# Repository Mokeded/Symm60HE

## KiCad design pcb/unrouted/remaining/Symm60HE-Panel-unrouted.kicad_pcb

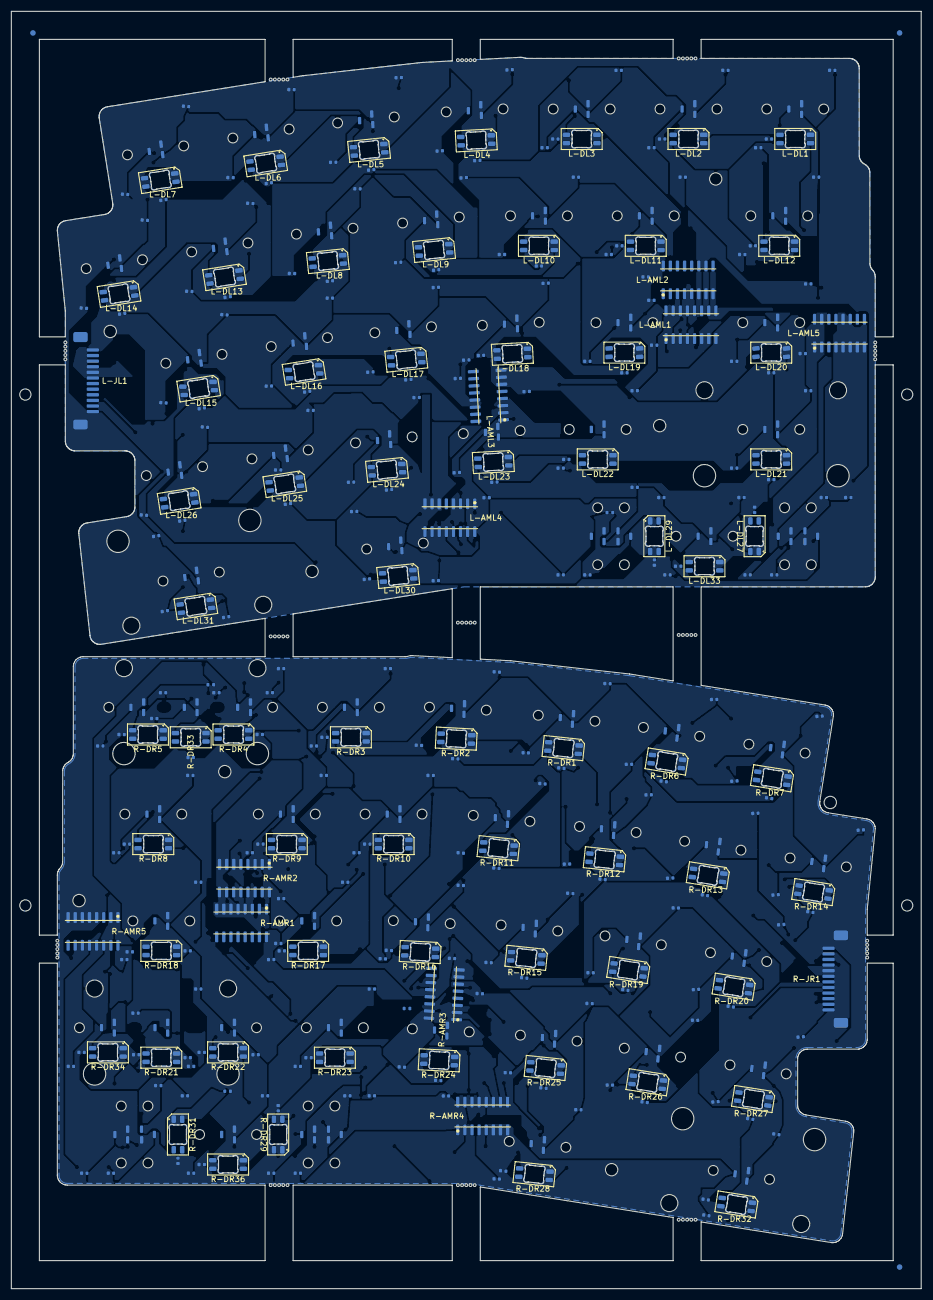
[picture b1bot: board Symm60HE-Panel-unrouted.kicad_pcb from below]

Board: 2 copper layers, 162.3 x 227.8 mm, 448 parts (366 on the bottom side), 154 nets, no tracks yet.

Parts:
FID1, FID2, FID3: FIDUCIAL_1MM_BCU; Fiducial_1mm_BCu
L-AML1, L-AML2, L-AML3, L-AML4, L-AML5: SN74LV4051A; AM1_SOIC-16_3.9x9.9mm_P1.27mm
L-CL1A, L-CL2A, L-CL3A, L-CL4A, L-CL5A, L-CL6A, L-CL7A, L-CL8A, L-CL9A, L-CL10A, L-CL11A, L-CL12A, L-CL13A, L-CL14A, L-CL15A, L-CL16A, L-CL17A, L-CL18A, L-CL19A, L-CL20A, L-CL21A, L-CL22A, L-CL23A, L-CL24A, L-CL25A, L-CL26A, L-CL27A, L-CL28A, L-CL29A, L-CL30A, L-CL31A, L-CL32A, L-CL33A: 100n; C1_C_0402_1005Metric
L-CL1B, L-CL2B, L-CL3B, L-CL4B, L-CL5B, L-CL6B, L-CL7B, L-CL8B, L-CL9B, L-CL10B, L-CL11B, L-CL12B, L-CL13B, L-CL14B, L-CL15B, L-CL16B, L-CL17B, L-CL18B, L-CL19B, L-CL20B, L-CL21B, L-CL22B, L-CL23B, L-CL24B, L-CL25B, L-CL26B, L-CL27B, L-CL28B, L-CL29B, L-CL30B, L-CL31B, L-CL32B, L-CL33B: 4.7n; C1_C_0402_1005Metric
L-CML1, L-CML2, L-CML3, L-CML4, L-CML5: 100n; C1_C_0402_1005Metric
L-CRGBL1, L-CRGBL2, L-CRGBL3, L-CRGBL4, L-CRGBL5, L-CRGBL6, L-CRGBL7, L-CRGBL8, L-CRGBL9, L-CRGBL10, L-CRGBL11, L-CRGBL12, L-CRGBL13, L-CRGBL14, L-CRGBL15, L-CRGBL16, L-CRGBL17, L-CRGBL18, L-CRGBL19, L-CRGBL20, L-CRGBL21, L-CRGBL22, L-CRGBL23, L-CRGBL24, L-CRGBL25, L-CRGBL26, L-CRGBL27, L-CRGBL29, L-CRGBL30, L-CRGBL31, L-CRGBL33: 100n; C1_C_0402_1005Metric
L-DL1, L-DL2, L-DL3, L-DL4, L-DL5, L-DL6, L-DL7, L-DL8, L-DL9, L-DL10, L-DL11, L-DL12, L-DL13, L-DL14, L-DL15, L-DL16, L-DL17, L-DL18, L-DL19, L-DL20, L-DL21, L-DL22, L-DL23, L-DL24, L-DL25, L-DL26, L-DL27, L-DL29, L-DL30, L-DL31, L-DL33: SK6812MINI-E; SK6812MINI-E_ReverseMount
L-HEL1, L-HEL2, L-HEL3, L-HEL4, L-HEL5, L-HEL6, L-HEL7, L-HEL9, L-HEL10, L-HEL11, L-HEL12, L-HEL13, L-HEL14, L-HEL16, L-HEL17, L-HEL18, L-HEL19, L-HEL20, L-HEL22, L-HEL23, L-HEL24, L-HEL25, L-HEL26, L-HEL27, L-HEL29, L-HEL31: MT9102ET; HE_KEY_1.00u
L-HEL8, L-HEL28, L-HEL30, L-HEL32: MT9102ET; HE_KEY_1.50u
L-HEL15: MT9102ET; HE_KEY_1.75u
L-HEL21, L-HEL33: MT9102ET; HE_KEY_2.25u
L-JL1: FFC_12P; FFC_12P_1.00mm_TopContact
L-MHL1, L-MHL2, L-MHL3, L-MHL4: M2_NPTH; MountingHole_2.2mm_M2_NPTH
L-RBPL29: 0R_DNP; R3_R_0402_1005Metric
L-SL1, L-SL2: STAB_MX; STABILIZER_MX_2U
MB1, MB2, MB3, MB4, MB5, MB6, MB7, MB8, MB9, MB10, MB11, MB12, MB13, MB14, MB15, MB16, MB17, MB18, MB19, MB20, MB21, MB22, MB23, MB24, MB25, MB26, MB27, MB28, MB29, MB30, MB31, MB32, MB33, MB34, MB35, MB36, MB37, MB38, MB39, MB40, MB41, MB42, MB43, MB44, MB45, MB46, MB47, MB48, MB49, MB50, MB51, MB52, MB53, MB54, MB55, MB56, MB57, MB58, MB59, MB60, MB61, MB62, MB63, MB64, MB65: MOUSE_BITE_0.5MM; MouseBite_0.5mm
R-AMR1, R-AMR2, R-AMR3, R-AMR4, R-AMR5: SN74LV4051A; AM1_SOIC-16_3.9x9.9mm_P1.27mm
R-CMR1, R-CMR2, R-CMR3, R-CMR4, R-CMR5: 100n; C1_C_0402_1005Metric
R-CR1A, R-CR2A, R-CR3A, R-CR4A, R-CR5A, R-CR6A, R-CR7A, R-CR8A, R-CR9A, R-CR10A, R-CR11A, R-CR12A, R-CR13A, R-CR14A, R-CR15A, R-CR16A, R-CR17A, R-CR18A, R-CR19A, R-CR20A, R-CR21A, R-CR22A, R-CR23A, R-CR24A, R-CR25A, R-CR26A, R-CR27A, R-CR28A, R-CR29A, R-CR30A, R-CR31A, R-CR32A, R-CR33A, R-CR34A, R-CR35A, R-CR36A: 100n; C1_C_0402_1005Metric
R-CR1B, R-CR2B, R-CR3B, R-CR4B, R-CR5B, R-CR6B, R-CR7B, R-CR8B, R-CR9B, R-CR10B, R-CR11B, R-CR12B, R-CR13B, R-CR14B, R-CR15B, R-CR16B, R-CR17B, R-CR18B, R-CR19B, R-CR20B, R-CR21B, R-CR22B, R-CR23B, R-CR24B, R-CR25B, R-CR26B, R-CR27B, R-CR28B, R-CR29B, R-CR30B, R-CR31B, R-CR32B, R-CR33B, R-CR34B, R-CR35B, R-CR36B: 4.7n; C1_C_0402_1005Metric
R-CRGBR1, R-CRGBR2, R-CRGBR3, R-CRGBR4, R-CRGBR5, R-CRGBR6, R-CRGBR7, R-CRGBR8, R-CRGBR9, R-CRGBR10, R-CRGBR11, R-CRGBR12, R-CRGBR13, R-CRGBR14, R-CRGBR15, R-CRGBR16, R-CRGBR17, R-CRGBR18, R-CRGBR19, R-CRGBR20, R-CRGBR21, R-CRGBR22, R-CRGBR23, R-CRGBR24, R-CRGBR25, R-CRGBR26, R-CRGBR27, R-CRGBR28, R-CRGBR29, R-CRGBR31, R-CRGBR32, R-CRGBR33, R-CRGBR34, R-CRGBR36: 100n; C1_C_0402_1005Metric
R-DR1, R-DR2, R-DR3, R-DR4, R-DR5, R-DR6, R-DR7, R-DR8, R-DR9, R-DR10, R-DR11, R-DR12, R-DR13, R-DR14, R-DR15, R-DR16, R-DR17, R-DR18, R-DR19, R-DR20, R-DR21, R-DR22, R-DR23, R-DR24, R-DR25, R-DR26, R-DR27, R-DR28, R-DR29, R-DR31, R-DR32, R-DR33, R-DR34, R-DR36: SK6812MINI-E; SK6812MINI-E_ReverseMount
R-HER1, R-HER2, R-HER3, R-HER5, R-HER6, R-HER7, R-HER8, R-HER9, R-HER10, R-HER12, R-HER13, R-HER14, R-HER15, R-HER16, R-HER17, R-HER19, R-HER20, R-HER21, R-HER22, R-HER23, R-HER24, R-HER27, R-HER28, R-HER29, R-HER30, R-HER32, R-HER34: MT9102ET; HE_KEY_1.00u
R-HER4: MT9102ET; HE_KEY_2.00u
R-HER11, R-HER31, R-HER33, R-HER35: MT9102ET; HE_KEY_1.50u
R-HER18: MT9102ET; HE_KEY_1.75u
R-HER25, R-HER36: MT9102ET; HE_KEY_2.25u
R-HER26: MT9102ET; HE_KEY_1.25u
R-JR1: FFC_12P; FFC_12P_1.00mm_TopContact
R-MHR1, R-MHR2, R-MHR3, R-MHR4: M2_NPTH; MountingHole_2.2mm_M2_NPTH
R-RBPR5, R-RBPR24, R-RBPR31: 0R_DNP; R3_R_0402_1005Metric
R-SR1, R-SR2, R-SR3: STAB_MX; STABILIZER_MX_2U
TH1, TH2, TH3, TH4: TOOLING_HOLE_2MM; ToolingHole_2mm_NPTH

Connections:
/L/+3V3A: L-AML1.16, L-AML2.16, L-AML3.16, L-AML4.16, L-AML5.16, L-CL1A.1, L-CL2A.1, L-CL3A.1, L-CL4A.1, L-CL5A.1, L-CL6A.1, L-CL7A.1, L-CL8A.1, L-CL9A.1, L-CL10A.1, L-CL11A.1, L-CL12A.1, L-CL13A.1, L-CL14A.1, L-CL15A.1, L-CL16A.1, L-CL17A.1, L-CL18A.1, L-CL19A.1, L-CL20A.1, L-CL21A.1, L-CL22A.1, L-CL23A.1, L-CL24A.1, L-CL25A.1, L-CL26A.1, L-CL27A.1, L-CL28A.1, L-CL29A.1, L-CL30A.1, L-CL31A.1, L-CL32A.1, L-CL33A.1, L-CML1.1, L-CML2.1, L-CML3.1, L-CML4.1, L-CML5.1, L-HEL1.1, L-HEL2.1, L-HEL3.1, L-HEL4.1, L-HEL5.1, L-HEL6.1, L-HEL7.1, L-HEL8.1, L-HEL9.1, L-HEL10.1, L-HEL11.1, L-HEL12.1, L-HEL13.1, L-HEL14.1, L-HEL15.1, L-HEL16.1, L-HEL17.1, L-HEL18.1, L-HEL19.1, L-HEL20.1, L-HEL21.1, L-HEL22.1, L-HEL23.1, L-HEL24.1, L-HEL25.1, L-HEL26.1, L-HEL27.1, L-HEL28.1, L-HEL29.1, L-HEL30.1, L-HEL31.1, L-HEL32.1, L-HEL33.1, L-JL1.12
/L/ADC_L1: L-AML1.3, L-JL1.6
/L/ADC_L2: L-AML2.3, L-JL1.4
/L/ADC_L3: L-AML3.3, L-JL1.2
/L/ADC_L4: L-AML4.3, L-JL1.1
/L/ADC_L5: L-AML5.3, L-JL1.11
/L/GND: L-AML1.6, L-AML1.7, L-AML1.8, L-AML2.6, L-AML2.7, L-AML2.8, L-AML3.6, L-AML3.7, L-AML3.8, L-AML4.4, L-AML4.6, L-AML4.7, L-AML4.8, L-AML5.1, L-AML5.2, L-AML5.4, L-AML5.5, L-AML5.6, L-AML5.7, L-AML5.8, L-AML5.12, L-AML5.15, L-CL1A.2, L-CL1B.2, L-CL2A.2, L-CL2B.2, L-CL3A.2, L-CL3B.2, L-CL4A.2, L-CL4B.2, L-CL5A.2, L-CL5B.2, L-CL6A.2, L-CL6B.2, L-CL7A.2, L-CL7B.2, L-CL8A.2, L-CL8B.2, L-CL9A.2, L-CL9B.2, L-CL10A.2, L-CL10B.2, L-CL11A.2, L-CL11B.2, L-CL12A.2, L-CL12B.2, L-CL13A.2, L-CL13B.2, L-CL14A.2, L-CL14B.2, L-CL15A.2, L-CL15B.2, L-CL16A.2, L-CL16B.2, L-CL17A.2, L-CL17B.2, L-CL18A.2, L-CL18B.2, L-CL19A.2, L-CL19B.2, L-CL20A.2, L-CL20B.2, L-CL21A.2, L-CL21B.2, L-CL22A.2, L-CL22B.2, L-CL23A.2, L-CL23B.2, L-CL24A.2, L-CL24B.2, L-CL25A.2, L-CL25B.2, L-CL26A.2, L-CL26B.2, L-CL27A.2, L-CL27B.2, L-CL28A.2, L-CL28B.2, L-CL29A.2, L-CL29B.2, L-CL30A.2, L-CL30B.2, L-CL31A.2, L-CL31B.2, L-CL32A.2, L-CL32B.2, L-CL33A.2, L-CL33B.2, L-CML1.2, L-CML2.2, L-CML3.2, L-CML4.2, L-CML5.2, L-CRGBL1.2, L-CRGBL2.2, L-CRGBL3.2, L-CRGBL4.2, L-CRGBL5.2, L-CRGBL6.2, L-CRGBL7.2, L-CRGBL8.2, L-CRGBL9.2, L-CRGBL10.2, L-CRGBL11.2, L-CRGBL12.2, L-CRGBL13.2, L-CRGBL14.2, L-CRGBL15.2, L-CRGBL16.2, L-CRGBL17.2, L-CRGBL18.2, L-CRGBL19.2, L-CRGBL20.2, L-CRGBL21.2, L-CRGBL22.2, L-CRGBL23.2, L-CRGBL24.2, L-CRGBL25.2, L-CRGBL26.2, L-CRGBL27.2, L-CRGBL29.2, L-CRGBL30.2, L-CRGBL31.2, L-CRGBL33.2, L-DL1.1, L-DL2.1, L-DL3.1, L-DL4.1, L-DL5.1, L-DL6.1, L-DL7.1, L-DL8.1, L-DL9.1, L-DL10.1, L-DL11.1, L-DL12.1, L-DL13.1, L-DL14.1, L-DL15.1, L-DL16.1, L-DL17.1, L-DL18.1, L-DL19.1, L-DL20.1, L-DL21.1, L-DL22.1, L-DL23.1, L-DL24.1, L-DL25.1, L-DL26.1, L-DL27.1, L-DL29.1, L-DL30.1, L-DL31.1, L-DL33.1, L-HEL1.2, L-HEL2.2, L-HEL3.2, L-HEL4.2, L-HEL5.2, L-HEL6.2, L-HEL7.2, L-HEL8.2, L-HEL9.2, L-HEL10.2, L-HEL11.2, L-HEL12.2, L-HEL13.2, L-HEL14.2, L-HEL15.2, L-HEL16.2, L-HEL17.2, L-HEL18.2, L-HEL19.2, L-HEL20.2, L-HEL21.2, L-HEL22.2, L-HEL23.2, L-HEL24.2, L-HEL25.2, L-HEL26.2, L-HEL27.2, L-HEL28.2, L-HEL29.2, L-HEL30.2, L-HEL31.2, L-HEL32.2, L-HEL33.2, L-JL1.5
/L/HE_L01: L-AML1.13, L-CL1B.1, L-HEL1.3
/L/HE_L02: L-AML1.14, L-CL2B.1, L-HEL2.3
/L/HE_L03: L-AML1.15, L-CL3B.1, L-HEL3.3
/L/HE_L04: L-AML1.12, L-CL4B.1, L-HEL4.3
/L/HE_L05: L-AML1.1, L-CL5B.1, L-HEL5.3
/L/HE_L06: L-AML1.5, L-CL6B.1, L-HEL6.3
/L/HE_L07: L-AML1.2, L-CL7B.1, L-HEL7.3
/L/HE_L08: L-AML1.4, L-CL8B.1, L-HEL8.3
/L/HE_L09: L-AML2.13, L-CL9B.1, L-HEL9.3
/L/HE_L10: L-AML2.14, L-CL10B.1, L-HEL10.3
/L/HE_L11: L-AML2.15, L-CL11B.1, L-HEL11.3
/L/HE_L12: L-AML2.12, L-CL12B.1, L-HEL12.3
/L/HE_L13: L-AML2.1, L-CL13B.1, L-HEL13.3
/L/HE_L14: L-AML2.5, L-CL14B.1, L-HEL14.3
/L/HE_L15: L-AML2.2, L-CL15B.1, L-HEL15.3
/L/HE_L16: L-AML2.4, L-CL16B.1, L-HEL16.3
/L/HE_L17: L-AML3.13, L-CL17B.1, L-HEL17.3
/L/HE_L18: L-AML3.14, L-CL18B.1, L-HEL18.3
/L/HE_L19: L-AML3.15, L-CL19B.1, L-HEL19.3
/L/HE_L20: L-AML3.12, L-CL20B.1, L-HEL20.3
/L/HE_L21: L-AML3.1, L-CL21B.1, L-HEL21.3
/L/HE_L22: L-AML3.5, L-CL22B.1, L-HEL22.3
/L/HE_L23: L-AML3.2, L-CL23B.1, L-HEL23.3
/L/HE_L24: L-AML3.4, L-CL24B.1, L-HEL24.3
/L/HE_L25: L-AML4.13, L-CL25B.1, L-HEL25.3
/L/HE_L26: L-AML4.14, L-CL26B.1, L-HEL26.3
/L/HE_L27: L-AML4.15, L-CL27B.1, L-HEL27.3
/L/HE_L28: L-AML4.12, L-CL29B.1, L-HEL29.3
/L/HE_L29: L-AML4.1, L-CL31B.1, L-HEL31.3
/L/HE_L30: L-AML4.5, L-CL32B.1, L-HEL32.3
/L/HE_L31: L-AML4.2, L-CL33B.1, L-HEL33.3
/L/HE_L32: L-AML5.13, L-CL28B.1, L-HEL28.3
/L/HE_L33: L-AML5.14, L-CL30B.1, L-HEL30.3
/L/MUX_A0: L-AML1.11, L-AML2.11, L-AML3.11, L-AML4.11, L-AML5.11, L-JL1.10
/L/MUX_A1: L-AML1.10, L-AML2.10, L-AML3.10, L-AML4.10, L-AML5.10, L-JL1.9
/L/MUX_A2: L-AML1.9, L-AML2.9, L-AML3.9, L-AML4.9, L-AML5.9, L-JL1.8
/L/RGB_L: L-DL1.2, L-JL1.3
/L/RGB_L_01: L-DL1.4, L-DL2.2
/L/RGB_L_02: L-DL2.4, L-DL3.2
/L/RGB_L_03: L-DL3.4, L-DL4.2
/L/RGB_L_04: L-DL4.4, L-DL5.2
/L/RGB_L_05: L-DL5.4, L-DL6.2
/L/RGB_L_06: L-DL6.4, L-DL7.2
/L/RGB_L_07: L-DL7.4, L-DL8.2
/L/RGB_L_08: L-DL8.4, L-DL9.2
/L/RGB_L_09: L-DL9.4, L-DL10.2
/L/RGB_L_10: L-DL10.4, L-DL11.2
/L/RGB_L_11: L-DL11.4, L-DL12.2
/L/RGB_L_12: L-DL12.4, L-DL13.2
/L/RGB_L_13: L-DL13.4, L-DL14.2
/L/RGB_L_14: L-DL14.4, L-DL15.2
/L/RGB_L_15: L-DL15.4, L-DL16.2
/L/RGB_L_16: L-DL16.4, L-DL17.2
/L/RGB_L_17: L-DL17.4, L-DL18.2
/L/RGB_L_18: L-DL18.4, L-DL19.2
/L/RGB_L_19: L-DL19.4, L-DL20.2
/L/RGB_L_20: L-DL20.4, L-DL21.2
/L/RGB_L_21: L-DL21.4, L-DL22.2
/L/RGB_L_22: L-DL22.4, L-DL23.2
/L/RGB_L_23: L-DL23.4, L-DL24.2
/L/RGB_L_24: L-DL24.4, L-DL25.2
/L/RGB_L_25: L-DL25.4, L-DL26.2
/L/RGB_L_26: L-DL26.4, L-DL27.2
/L/RGB_L_27: L-DL27.4, L-DL33.2
/L/RGB_L_28: L-DL29.2, L-DL33.4, L-RBPL29.1
/L/RGB_L_29: L-DL29.4, L-DL30.2, L-RBPL29.2
/L/RGB_L_30: L-DL30.4, L-DL31.2
/L/VBUS: L-CRGBL1.1, L-CRGBL2.1, L-CRGBL3.1, L-CRGBL4.1, L-CRGBL5.1, L-CRGBL6.1, L-CRGBL7.1, L-CRGBL8.1, L-CRGBL9.1, L-CRGBL10.1, L-CRGBL11.1, L-CRGBL12.1, L-CRGBL13.1, L-CRGBL14.1, L-CRGBL15.1, L-CRGBL16.1, L-CRGBL17.1, L-CRGBL18.1, L-CRGBL19.1, L-CRGBL20.1, L-CRGBL21.1, L-CRGBL22.1, L-CRGBL23.1, L-CRGBL24.1, L-CRGBL25.1, L-CRGBL26.1, L-CRGBL27.1, L-CRGBL29.1, L-CRGBL30.1, L-CRGBL31.1, L-CRGBL33.1, L-DL1.3, L-DL2.3, L-DL3.3, L-DL4.3, L-DL5.3, L-DL6.3, L-DL7.3, L-DL8.3, L-DL9.3, L-DL10.3, L-DL11.3, L-DL12.3, L-DL13.3, L-DL14.3, L-DL15.3, L-DL16.3, L-DL17.3, L-DL18.3, L-DL19.3, L-DL20.3, L-DL21.3, L-DL22.3, L-DL23.3, L-DL24.3, L-DL25.3, L-DL26.3, L-DL27.3, L-DL29.3, L-DL30.3, L-DL31.3, L-DL33.3, L-JL1.7
/R/+3V3A: R-AMR1.16, R-AMR2.16, R-AMR3.16, R-AMR4.16, R-AMR5.16, R-CMR1.1, R-CMR2.1, R-CMR3.1, R-CMR4.1, R-CMR5.1, R-CR1A.1, R-CR2A.1, R-CR3A.1, R-CR4A.1, R-CR5A.1, R-CR6A.1, R-CR7A.1, R-CR8A.1, R-CR9A.1, R-CR10A.1, R-CR11A.1, R-CR12A.1, R-CR13A.1, R-CR14A.1, R-CR15A.1, R-CR16A.1, R-CR17A.1, R-CR18A.1, R-CR19A.1, R-CR20A.1, R-CR21A.1, R-CR22A.1, R-CR23A.1, R-CR24A.1, R-CR25A.1, R-CR26A.1, R-CR27A.1, R-CR28A.1, R-CR29A.1, R-CR30A.1, R-CR31A.1, R-CR32A.1, R-CR33A.1, R-CR34A.1, R-CR35A.1, R-CR36A.1, R-HER1.1, R-HER2.1, R-HER3.1, R-HER4.1, R-HER5.1, R-HER6.1, R-HER7.1, R-HER8.1, R-HER9.1, R-HER10.1, R-HER11.1, R-HER12.1, R-HER13.1, R-HER14.1, R-HER15.1, R-HER16.1, R-HER17.1, R-HER18.1, R-HER19.1, R-HER20.1, R-HER21.1, R-HER22.1, R-HER23.1, R-HER24.1, R-HER25.1, R-HER26.1, R-HER27.1, R-HER28.1, R-HER29.1, R-HER30.1, R-HER31.1, R-HER32.1, R-HER33.1, R-HER34.1, R-HER35.1, R-HER36.1, R-JR1.1
/R/ADC_R1: R-AMR1.3, R-JR1.7
/R/ADC_R2: R-AMR2.3, R-JR1.9
/R/ADC_R3: R-AMR3.3, R-JR1.11
/R/ADC_R4: R-AMR4.3, R-JR1.12
/R/ADC_R5: R-AMR5.3, R-JR1.2
/R/GND: R-AMR1.6, R-AMR1.7, R-AMR1.8, R-AMR2.6, R-AMR2.7, R-AMR2.8, R-AMR3.6, R-AMR3.7, R-AMR3.8, R-AMR4.6, R-AMR4.7, R-AMR4.8, R-AMR5.1, R-AMR5.2, R-AMR5.4, R-AMR5.5, R-AMR5.6, R-AMR5.7, R-AMR5.8, R-CMR1.2, R-CMR2.2, R-CMR3.2, R-CMR4.2, R-CMR5.2, R-CR1A.2, R-CR1B.2, R-CR2A.2, R-CR2B.2, R-CR3A.2, R-CR3B.2, R-CR4A.2, R-CR4B.2, R-CR5A.2, R-CR5B.2, R-CR6A.2, R-CR6B.2, R-CR7A.2, R-CR7B.2, R-CR8A.2, R-CR8B.2, R-CR9A.2, R-CR9B.2, R-CR10A.2, R-CR10B.2, R-CR11A.2, R-CR11B.2, R-CR12A.2, R-CR12B.2, R-CR13A.2, R-CR13B.2, R-CR14A.2, R-CR14B.2, R-CR15A.2, R-CR15B.2, R-CR16A.2, R-CR16B.2, R-CR17A.2, R-CR17B.2, R-CR18A.2, R-CR18B.2, R-CR19A.2, R-CR19B.2, R-CR20A.2, R-CR20B.2, R-CR21A.2, R-CR21B.2, R-CR22A.2, R-CR22B.2, R-CR23A.2, R-CR23B.2, R-CR24A.2, R-CR24B.2, R-CR25A.2, R-CR25B.2, R-CR26A.2, R-CR26B.2, R-CR27A.2, R-CR27B.2, R-CR28A.2, R-CR28B.2, R-CR29A.2, R-CR29B.2, R-CR30A.2, R-CR30B.2, R-CR31A.2, R-CR31B.2, R-CR32A.2, R-CR32B.2, R-CR33A.2, R-CR33B.2, R-CR34A.2, R-CR34B.2, R-CR35A.2, R-CR35B.2, R-CR36A.2, R-CR36B.2, R-CRGBR1.2, R-CRGBR2.2, R-CRGBR3.2, R-CRGBR4.2, R-CRGBR5.2, R-CRGBR6.2, R-CRGBR7.2, R-CRGBR8.2, R-CRGBR9.2, R-CRGBR10.2, R-CRGBR11.2, R-CRGBR12.2, R-CRGBR13.2, R-CRGBR14.2, R-CRGBR15.2, R-CRGBR16.2, R-CRGBR17.2, R-CRGBR18.2, R-CRGBR19.2, R-CRGBR20.2, R-CRGBR21.2, R-CRGBR22.2, R-CRGBR23.2, R-CRGBR24.2, R-CRGBR25.2, R-CRGBR26.2, R-CRGBR27.2, R-CRGBR28.2, R-CRGBR29.2, R-CRGBR31.2, R-CRGBR32.2, R-CRGBR33.2, R-CRGBR34.2, R-CRGBR36.2, R-DR1.1, R-DR2.1, R-DR3.1, R-DR4.1, R-DR5.1, R-DR6.1, R-DR7.1, R-DR8.1, R-DR9.1, R-DR10.1, R-DR11.1, R-DR12.1, R-DR13.1, R-DR14.1, R-DR15.1, R-DR16.1, R-DR17.1, R-DR18.1, R-DR19.1, R-DR20.1, R-DR21.1, R-DR22.1, R-DR23.1, R-DR24.1, R-DR25.1, R-DR26.1, R-DR27.1, R-DR28.1, R-DR29.1, R-DR31.1, R-DR32.1, R-DR33.1, R-DR34.1, R-DR36.1, R-HER1.2, R-HER2.2, R-HER3.2, R-HER4.2, R-HER5.2, R-HER6.2, R-HER7.2, R-HER8.2, R-HER9.2, R-HER10.2, R-HER11.2, R-HER12.2, R-HER13.2, R-HER14.2, R-HER15.2, R-HER16.2, R-HER17.2, R-HER18.2, R-HER19.2, R-HER20.2, R-HER21.2, R-HER22.2, R-HER23.2, R-HER24.2, R-HER25.2, R-HER26.2, R-HER27.2, R-HER28.2, R-HER29.2, R-HER30.2, R-HER31.2, R-HER32.2, R-HER33.2, R-HER34.2, R-HER35.2, R-HER36.2, R-JR1.8
/R/HE_R01: R-AMR1.13, R-CR6B.1, R-HER6.3
/R/HE_R02: R-AMR1.14, R-CR1B.1, R-HER1.3
/R/HE_R03: R-AMR1.15, R-CR2B.1, R-HER2.3
/R/HE_R04: R-AMR1.12, R-CR3B.1, R-HER3.3
/R/HE_R05: R-AMR1.1, R-CR5B.1, R-HER5.3
/R/HE_R06: R-AMR1.5, R-CR7B.1, R-HER7.3
/R/HE_R07: R-AMR1.2, R-CR8B.1, R-HER8.3
/R/HE_R08: R-AMR1.4, R-CR13B.1, R-HER13.3
/R/HE_R09: R-AMR2.13, R-CR12B.1, R-HER12.3
/R/HE_R10: R-AMR2.14, R-CR9B.1, R-HER9.3
/R/HE_R11: R-AMR2.15, R-CR10B.1, R-HER10.3
/R/HE_R12: R-AMR2.12, R-CR11B.1, R-HER11.3
/R/HE_R13: R-AMR2.1, R-CR14B.1, R-HER14.3
/R/HE_R14: R-AMR2.5, R-CR15B.1, R-HER15.3
/R/HE_R15: R-AMR2.2, R-CR19B.1, R-HER19.3
/R/HE_R16: R-AMR2.4, R-CR16B.1, R-HER16.3
/R/HE_R17: R-AMR3.13, R-CR17B.1, R-HER17.3
/R/HE_R18: R-AMR3.14, R-CR18B.1, R-HER18.3
/R/HE_R19: R-AMR3.15, R-CR20B.1, R-HER20.3
/R/HE_R20: R-AMR3.12, R-CR21B.1, R-HER21.3
/R/HE_R21: R-AMR3.1, R-CR27B.1, R-HER27.3
/R/HE_R22: R-AMR3.5, R-CR22B.1, R-HER22.3
/R/HE_R23: R-AMR3.2, R-CR23B.1, R-HER23.3
/R/HE_R24: R-AMR3.4, R-CR24B.1, R-HER24.3
/R/HE_R25: R-AMR4.13, R-CR25B.1, R-HER25.3
/R/HE_R26: R-AMR4.14, R-CR28B.1, R-HER28.3
/R/HE_R27: R-AMR4.15, R-CR29B.1, R-HER29.3
/R/HE_R28: R-AMR4.12, R-CR35B.1, R-HER35.3
/R/HE_R29: R-AMR4.1, R-CR30B.1, R-HER30.3
/R/HE_R30: R-AMR4.5, R-CR32B.1, R-HER32.3
/R/HE_R31: R-AMR4.2, R-CR34B.1, R-HER34.3
/R/HE_R32: R-AMR4.4, R-CR36B.1, R-HER36.3
/R/HE_R33: R-AMR5.13, R-CR4B.1, R-HER4.3
/R/HE_R34: R-AMR5.14, R-CR26B.1, R-HER26.3
/R/HE_R35: R-AMR5.15, R-CR31B.1, R-HER31.3
/R/HE_R36: R-AMR5.12, R-CR33B.1, R-HER33.3
/R/MUX_A0: R-AMR1.11, R-AMR2.11, R-AMR3.11, R-AMR4.11, R-AMR5.11, R-JR1.3
/R/MUX_A1: R-AMR1.10, R-AMR2.10, R-AMR3.10, R-AMR4.10, R-AMR5.10, R-JR1.4
/R/MUX_A2: R-AMR1.9, R-AMR2.9, R-AMR3.9, R-AMR4.9, R-AMR5.9, R-JR1.5
/R/RGB_R: R-DR1.2, R-JR1.10
/R/RGB_R_01: R-DR1.4, R-DR2.2
/R/RGB_R_02: R-DR2.4, R-DR3.2
/R/RGB_R_03: R-DR3.4, R-DR4.2, R-DR33.2
/R/RGB_R_04: R-DR4.4, R-DR5.2, R-DR33.4, R-RBPR5.1
/R/RGB_R_05: R-DR5.4, R-DR6.2, R-RBPR5.2
/R/RGB_R_06: R-DR6.4, R-DR7.2
/R/RGB_R_07: R-DR7.4, R-DR8.2
/R/RGB_R_08: R-DR8.4, R-DR9.2
/R/RGB_R_09: R-DR9.4, R-DR10.2
/R/RGB_R_10: R-DR10.4, R-DR11.2
/R/RGB_R_11: R-DR11.4, R-DR12.2
/R/RGB_R_12: R-DR12.4, R-DR13.2
/R/RGB_R_13: R-DR13.4, R-DR14.2
/R/RGB_R_14: R-DR14.4, R-DR15.2
/R/RGB_R_15: R-DR15.4, R-DR16.2
/R/RGB_R_16: R-DR16.4, R-DR17.2
/R/RGB_R_17: R-DR17.4, R-DR18.2
/R/RGB_R_18: R-DR18.4, R-DR19.2
/R/RGB_R_19: R-DR19.4, R-DR20.2
/R/RGB_R_20: R-DR20.4, R-DR21.2, R-DR34.2
/R/RGB_R_21: R-DR21.4, R-DR22.2, R-DR34.4
/R/RGB_R_22: R-DR22.4, R-DR23.2
/R/RGB_R_23: R-DR23.4, R-DR24.2, R-RBPR24.1
/R/RGB_R_24: R-DR24.4, R-DR25.2, R-RBPR24.2
/R/RGB_R_25: R-DR25.4, R-DR26.2
/R/RGB_R_26: R-DR26.4, R-DR27.2
/R/RGB_R_27: R-DR27.4, R-DR28.2
/R/RGB_R_28: R-DR28.4, R-DR29.2
/R/RGB_R_29: R-DR29.4, R-DR36.2
/R/RGB_R_30: R-DR31.2, R-DR36.4, R-RBPR31.1
/R/RGB_R_31: R-DR31.4, R-DR32.2, R-RBPR31.2
/R/VBUS: R-CRGBR1.1, R-CRGBR2.1, R-CRGBR3.1, R-CRGBR4.1, R-CRGBR5.1, R-CRGBR6.1, R-CRGBR7.1, R-CRGBR8.1, R-CRGBR9.1, R-CRGBR10.1, R-CRGBR11.1, R-CRGBR12.1, R-CRGBR13.1, R-CRGBR14.1, R-CRGBR15.1, R-CRGBR16.1, R-CRGBR17.1, R-CRGBR18.1, R-CRGBR19.1, R-CRGBR20.1, R-CRGBR21.1, R-CRGBR22.1, R-CRGBR23.1, R-CRGBR24.1, R-CRGBR25.1, R-CRGBR26.1, R-CRGBR27.1, R-CRGBR28.1, R-CRGBR29.1, R-CRGBR31.1, R-CRGBR32.1, R-CRGBR33.1, R-CRGBR34.1, R-CRGBR36.1, R-DR1.3, R-DR2.3, R-DR3.3, R-DR4.3, R-DR5.3, R-DR6.3, R-DR7.3, R-DR8.3, R-DR9.3, R-DR10.3, R-DR11.3, R-DR12.3, R-DR13.3, R-DR14.3, R-DR15.3, R-DR16.3, R-DR17.3, R-DR18.3, R-DR19.3, R-DR20.3, R-DR21.3, R-DR22.3, R-DR23.3, R-DR24.3, R-DR25.3, R-DR26.3, R-DR27.3, R-DR28.3, R-DR29.3, R-DR31.3, R-DR32.3, R-DR33.3, R-DR34.3, R-DR36.3, R-JR1.6

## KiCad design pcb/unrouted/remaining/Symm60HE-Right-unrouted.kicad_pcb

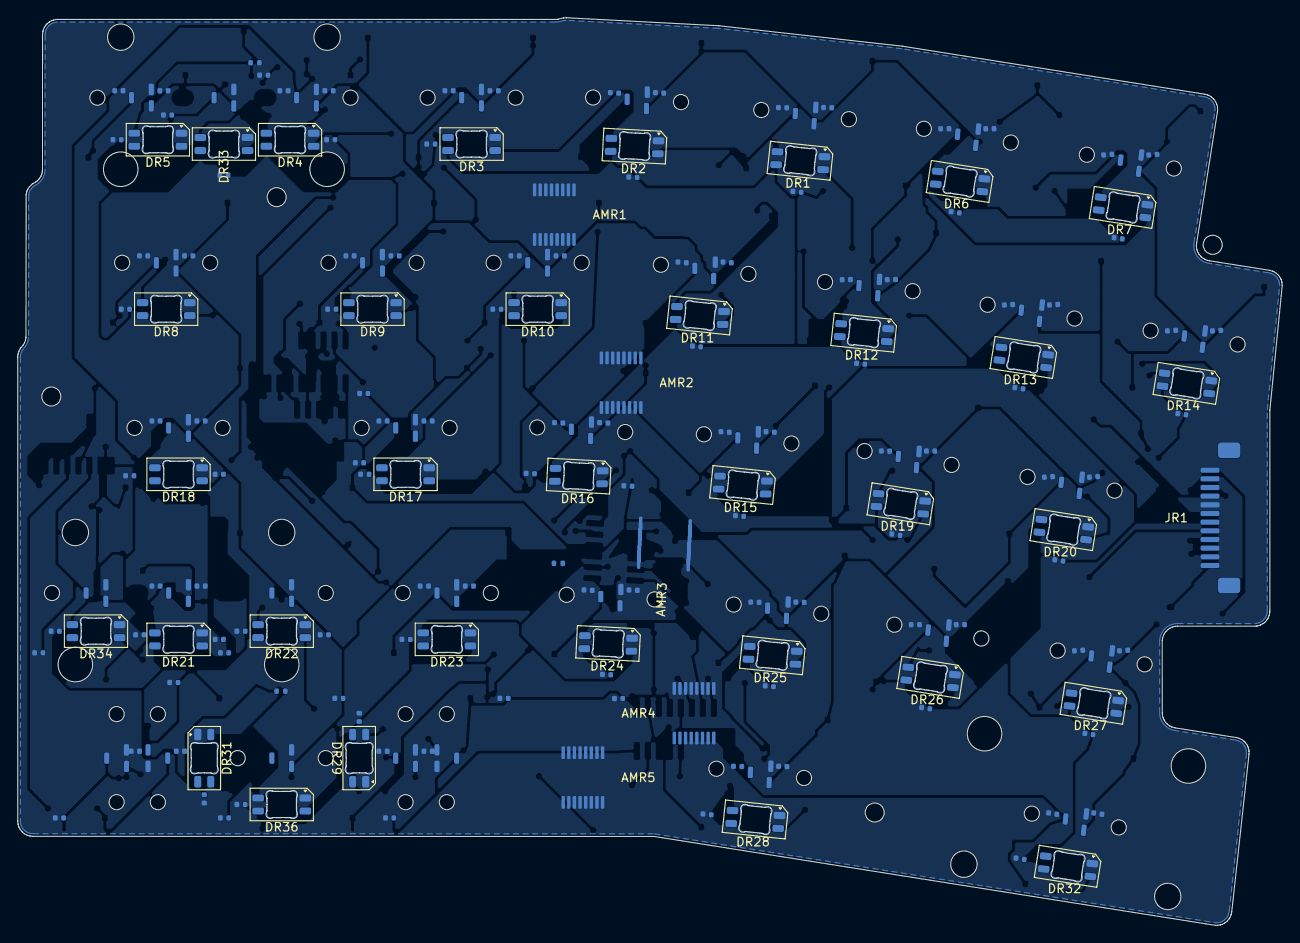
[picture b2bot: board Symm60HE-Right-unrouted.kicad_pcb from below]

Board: 2 copper layers, 145.9 x 104.7 mm, 197 parts (190 on the bottom side), 79 nets, no tracks yet.

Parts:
AMR1, AMR2, AMR3, AMR4, AMR5: SN74LV4051A; AM1_TSSOP-16_4.4x5mm_P0.65mm
CMR1, CMR2, CMR3, CMR4, CMR5: 100n; C1_C_0402_1005Metric
CR1A, CR2A, CR3A, CR4A, CR5A, CR6A, CR7A, CR8A, CR9A, CR10A, CR11A, CR12A, CR13A, CR14A, CR15A, CR16A, CR17A, CR18A, CR19A, CR20A, CR21A, CR22A, CR23A, CR24A, CR25A, CR26A, CR27A, CR28A, CR29A, CR30A, CR31A, CR32A, CR33A, CR34A, CR35A, CR36A: 100n; C1_C_0402_1005Metric
CR1B, CR2B, CR3B, CR4B, CR5B, CR6B, CR7B, CR8B, CR9B, CR10B, CR11B, CR12B, CR13B, CR14B, CR15B, CR16B, CR17B, CR18B, CR19B, CR20B, CR21B, CR22B, CR23B, CR24B, CR25B, CR26B, CR27B, CR28B, CR29B, CR30B, CR31B, CR32B, CR33B, CR34B, CR35B, CR36B: 4.7n; C1_C_0402_1005Metric
CRGBR1, CRGBR2, CRGBR3, CRGBR4, CRGBR5, CRGBR6, CRGBR7, CRGBR8, CRGBR9, CRGBR10, CRGBR11, CRGBR12, CRGBR13, CRGBR14, CRGBR15, CRGBR16, CRGBR17, CRGBR18, CRGBR19, CRGBR20, CRGBR21, CRGBR22, CRGBR23, CRGBR24, CRGBR25, CRGBR26, CRGBR27, CRGBR28, CRGBR29, CRGBR31, CRGBR32, CRGBR33, CRGBR34, CRGBR36: 100n; C1_C_0402_1005Metric
DR1, DR2, DR3, DR4, DR5, DR6, DR7, DR8, DR9, DR10, DR11, DR12, DR13, DR14, DR15, DR16, DR17, DR18, DR19, DR20, DR21, DR22, DR23, DR24, DR25, DR26, DR27, DR28, DR29, DR31, DR32, DR33, DR34, DR36: SK6812MINI-E; SK6812MINI-E_ReverseMount
HER1, HER2, HER3, HER5, HER6, HER7, HER8, HER9, HER10, HER12, HER13, HER14, HER15, HER16, HER17, HER19, HER20, HER21, HER22, HER23, HER24, HER27, HER28, HER29, HER30, HER32, HER34: MT9102ET; HE_KEY_1.00u
HER4: MT9102ET; HE_KEY_2.00u
HER11, HER31, HER33, HER35: MT9102ET; HE_KEY_1.50u
HER18: MT9102ET; HE_KEY_1.75u
HER25, HER36: MT9102ET; HE_KEY_2.25u
HER26: MT9102ET; HE_KEY_1.25u
JR1: FFC_12P; FFC_12P_1.00mm_TopContact
MHR1, MHR2, MHR3, MHR4: M2_NPTH; MountingHole_2.2mm_M2_NPTH
RBPR5, RBPR24, RBPR31: 0R_DNP; R3_R_0402_1005Metric
SR1, SR2, SR3: STAB_MX; STABILIZER_MX_2U

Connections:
+3V3A: AMR1.16, AMR2.16, AMR3.16, AMR4.16, AMR5.16, CMR1.1, CMR2.1, CMR3.1, CMR4.1, CMR5.1, CR1A.1, CR2A.1, CR3A.1, CR4A.1, CR5A.1, CR6A.1, CR7A.1, CR8A.1, CR9A.1, CR10A.1, CR11A.1, CR12A.1, CR13A.1, CR14A.1, CR15A.1, CR16A.1, CR17A.1, CR18A.1, CR19A.1, CR20A.1, CR21A.1, CR22A.1, CR23A.1, CR24A.1, CR25A.1, CR26A.1, CR27A.1, CR28A.1, CR29A.1, CR30A.1, CR31A.1, CR32A.1, CR33A.1, CR34A.1, CR35A.1, CR36A.1, HER1.1, HER2.1, HER3.1, HER4.1, HER5.1, HER6.1, HER7.1, HER8.1, HER9.1, HER10.1, HER11.1, HER12.1, HER13.1, HER14.1, HER15.1, HER16.1, HER17.1, HER18.1, HER19.1, HER20.1, HER21.1, HER22.1, HER23.1, HER24.1, HER25.1, HER26.1, HER27.1, HER28.1, HER29.1, HER30.1, HER31.1, HER32.1, HER33.1, HER34.1, HER35.1, HER36.1, JR1.1
ADC_R1: AMR1.3, JR1.7
ADC_R2: AMR2.3, JR1.9
ADC_R3: AMR3.3, JR1.11
ADC_R4: AMR4.3, JR1.12
ADC_R5: AMR5.3, JR1.2
GND: AMR1.6, AMR1.7, AMR1.8, AMR2.6, AMR2.7, AMR2.8, AMR3.6, AMR3.7, AMR3.8, AMR4.6, AMR4.7, AMR4.8, AMR5.1, AMR5.2, AMR5.4, AMR5.5, AMR5.6, AMR5.7, AMR5.8, CMR1.2, CMR2.2, CMR3.2, CMR4.2, CMR5.2, CR1A.2, CR1B.2, CR2A.2, CR2B.2, CR3A.2, CR3B.2, CR4A.2, CR4B.2, CR5A.2, CR5B.2, CR6A.2, CR6B.2, CR7A.2, CR7B.2, CR8A.2, CR8B.2, CR9A.2, CR9B.2, CR10A.2, CR10B.2, CR11A.2, CR11B.2, CR12A.2, CR12B.2, CR13A.2, CR13B.2, CR14A.2, CR14B.2, CR15A.2, CR15B.2, CR16A.2, CR16B.2, CR17A.2, CR17B.2, CR18A.2, CR18B.2, CR19A.2, CR19B.2, CR20A.2, CR20B.2, CR21A.2, CR21B.2, CR22A.2, CR22B.2, CR23A.2, CR23B.2, CR24A.2, CR24B.2, CR25A.2, CR25B.2, CR26A.2, CR26B.2, CR27A.2, CR27B.2, CR28A.2, CR28B.2, CR29A.2, CR29B.2, CR30A.2, CR30B.2, CR31A.2, CR31B.2, CR32A.2, CR32B.2, CR33A.2, CR33B.2, CR34A.2, CR34B.2, CR35A.2, CR35B.2, CR36A.2, CR36B.2, CRGBR1.2, CRGBR2.2, CRGBR3.2, CRGBR4.2, CRGBR5.2, CRGBR6.2, CRGBR7.2, CRGBR8.2, CRGBR9.2, CRGBR10.2, CRGBR11.2, CRGBR12.2, CRGBR13.2, CRGBR14.2, CRGBR15.2, CRGBR16.2, CRGBR17.2, CRGBR18.2, CRGBR19.2, CRGBR20.2, CRGBR21.2, CRGBR22.2, CRGBR23.2, CRGBR24.2, CRGBR25.2, CRGBR26.2, CRGBR27.2, CRGBR28.2, CRGBR29.2, CRGBR31.2, CRGBR32.2, CRGBR33.2, CRGBR34.2, CRGBR36.2, DR1.1, DR2.1, DR3.1, DR4.1, DR5.1, DR6.1, DR7.1, DR8.1, DR9.1, DR10.1, DR11.1, DR12.1, DR13.1, DR14.1, DR15.1, DR16.1, DR17.1, DR18.1, DR19.1, DR20.1, DR21.1, DR22.1, DR23.1, DR24.1, DR25.1, DR26.1, DR27.1, DR28.1, DR29.1, DR31.1, DR32.1, DR33.1, DR34.1, DR36.1, HER1.2, HER2.2, HER3.2, HER4.2, HER5.2, HER6.2, HER7.2, HER8.2, HER9.2, HER10.2, HER11.2, HER12.2, HER13.2, HER14.2, HER15.2, HER16.2, HER17.2, HER18.2, HER19.2, HER20.2, HER21.2, HER22.2, HER23.2, HER24.2, HER25.2, HER26.2, HER27.2, HER28.2, HER29.2, HER30.2, HER31.2, HER32.2, HER33.2, HER34.2, HER35.2, HER36.2, JR1.8
HE_R01: AMR1.13, CR6B.1, HER6.3
HE_R02: AMR1.14, CR1B.1, HER1.3
HE_R03: AMR1.15, CR2B.1, HER2.3
HE_R04: AMR1.12, CR3B.1, HER3.3
HE_R05: AMR1.1, CR5B.1, HER5.3
HE_R06: AMR1.5, CR7B.1, HER7.3
HE_R07: AMR1.2, CR8B.1, HER8.3
HE_R08: AMR1.4, CR13B.1, HER13.3
HE_R09: AMR2.13, CR12B.1, HER12.3
HE_R10: AMR2.14, CR9B.1, HER9.3
HE_R11: AMR2.15, CR10B.1, HER10.3
HE_R12: AMR2.12, CR11B.1, HER11.3
HE_R13: AMR2.1, CR14B.1, HER14.3
HE_R14: AMR2.5, CR15B.1, HER15.3
HE_R15: AMR2.2, CR19B.1, HER19.3
HE_R16: AMR2.4, CR16B.1, HER16.3
HE_R17: AMR3.13, CR17B.1, HER17.3
HE_R18: AMR3.14, CR18B.1, HER18.3
HE_R19: AMR3.15, CR20B.1, HER20.3
HE_R20: AMR3.12, CR21B.1, HER21.3
HE_R21: AMR3.1, CR27B.1, HER27.3
HE_R22: AMR3.5, CR22B.1, HER22.3
HE_R23: AMR3.2, CR23B.1, HER23.3
HE_R24: AMR3.4, CR24B.1, HER24.3
HE_R25: AMR4.13, CR25B.1, HER25.3
HE_R26: AMR4.14, CR28B.1, HER28.3
HE_R27: AMR4.15, CR29B.1, HER29.3
HE_R28: AMR4.12, CR35B.1, HER35.3
HE_R29: AMR4.1, CR30B.1, HER30.3
HE_R30: AMR4.5, CR32B.1, HER32.3
HE_R31: AMR4.2, CR34B.1, HER34.3
HE_R32: AMR4.4, CR36B.1, HER36.3
HE_R33: AMR5.13, CR4B.1, HER4.3
HE_R34: AMR5.14, CR26B.1, HER26.3
HE_R35: AMR5.15, CR31B.1, HER31.3
HE_R36: AMR5.12, CR33B.1, HER33.3
MUX_A0: AMR1.11, AMR2.11, AMR3.11, AMR4.11, AMR5.11, JR1.3
MUX_A1: AMR1.10, AMR2.10, AMR3.10, AMR4.10, AMR5.10, JR1.4
MUX_A2: AMR1.9, AMR2.9, AMR3.9, AMR4.9, AMR5.9, JR1.5
RGB_R: DR1.2, JR1.10
RGB_R_01: DR1.4, DR2.2
RGB_R_02: DR2.4, DR3.2
RGB_R_03: DR3.4, DR4.2, DR33.2
RGB_R_04: DR4.4, DR5.2, DR33.4, RBPR5.1
RGB_R_05: DR5.4, DR6.2, RBPR5.2
RGB_R_06: DR6.4, DR7.2
RGB_R_07: DR7.4, DR8.2
RGB_R_08: DR8.4, DR9.2
RGB_R_09: DR9.4, DR10.2
RGB_R_10: DR10.4, DR11.2
RGB_R_11: DR11.4, DR12.2
RGB_R_12: DR12.4, DR13.2
RGB_R_13: DR13.4, DR14.2
RGB_R_14: DR14.4, DR15.2
RGB_R_15: DR15.4, DR16.2
RGB_R_16: DR16.4, DR17.2
RGB_R_17: DR17.4, DR18.2
RGB_R_18: DR18.4, DR19.2
RGB_R_19: DR19.4, DR20.2
RGB_R_20: DR20.4, DR21.2, DR34.2
RGB_R_21: DR21.4, DR22.2, DR34.4
RGB_R_22: DR22.4, DR23.2
RGB_R_23: DR23.4, DR24.2, RBPR24.1
RGB_R_24: DR24.4, DR25.2, RBPR24.2
RGB_R_25: DR25.4, DR26.2
RGB_R_26: DR26.4, DR27.2
RGB_R_27: DR27.4, DR28.2
RGB_R_28: DR28.4, DR29.2
RGB_R_29: DR29.4, DR36.2
RGB_R_30: DR31.2, DR36.4, RBPR31.1
RGB_R_31: DR31.4, DR32.2, RBPR31.2
VBUS: CRGBR1.1, CRGBR2.1, CRGBR3.1, CRGBR4.1, CRGBR5.1, CRGBR6.1, CRGBR7.1, CRGBR8.1, CRGBR9.1, CRGBR10.1, CRGBR11.1, CRGBR12.1, CRGBR13.1, CRGBR14.1, CRGBR15.1, CRGBR16.1, CRGBR17.1, CRGBR18.1, CRGBR19.1, CRGBR20.1, CRGBR21.1, CRGBR22.1, CRGBR23.1, CRGBR24.1, CRGBR25.1, CRGBR26.1, CRGBR27.1, CRGBR28.1, CRGBR29.1, CRGBR31.1, CRGBR32.1, CRGBR33.1, CRGBR34.1, CRGBR36.1, DR1.3, DR2.3, DR3.3, DR4.3, DR5.3, DR6.3, DR7.3, DR8.3, DR9.3, DR10.3, DR11.3, DR12.3, DR13.3, DR14.3, DR15.3, DR16.3, DR17.3, DR18.3, DR19.3, DR20.3, DR21.3, DR22.3, DR23.3, DR24.3, DR25.3, DR26.3, DR27.3, DR28.3, DR29.3, DR31.3, DR32.3, DR33.3, DR34.3, DR36.3, JR1.6
